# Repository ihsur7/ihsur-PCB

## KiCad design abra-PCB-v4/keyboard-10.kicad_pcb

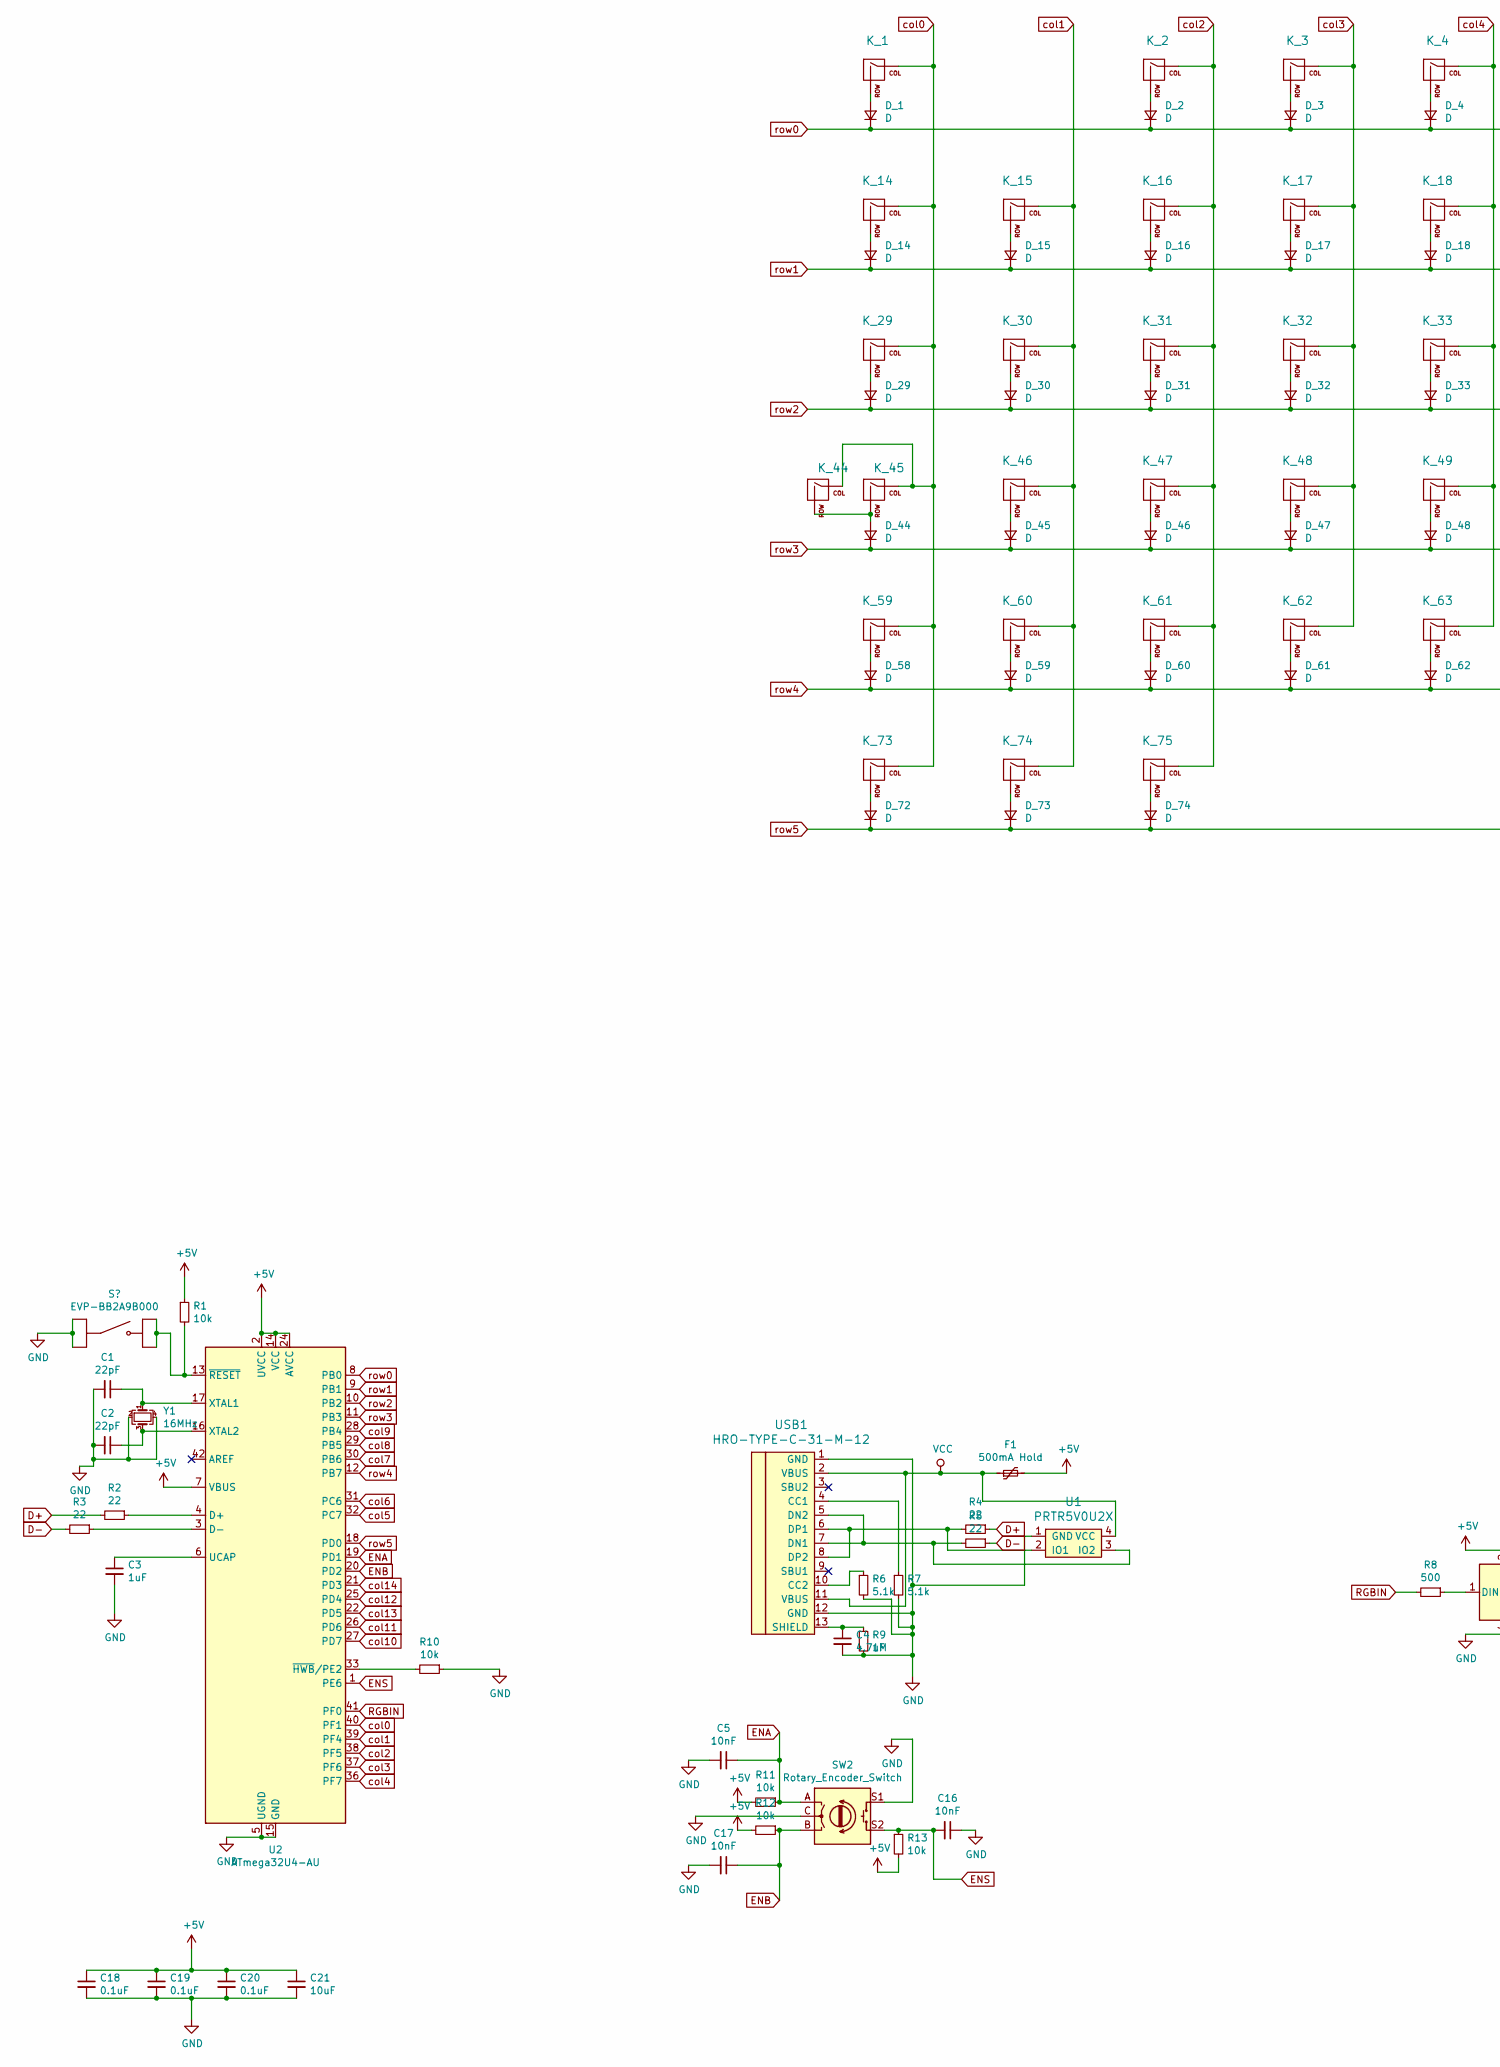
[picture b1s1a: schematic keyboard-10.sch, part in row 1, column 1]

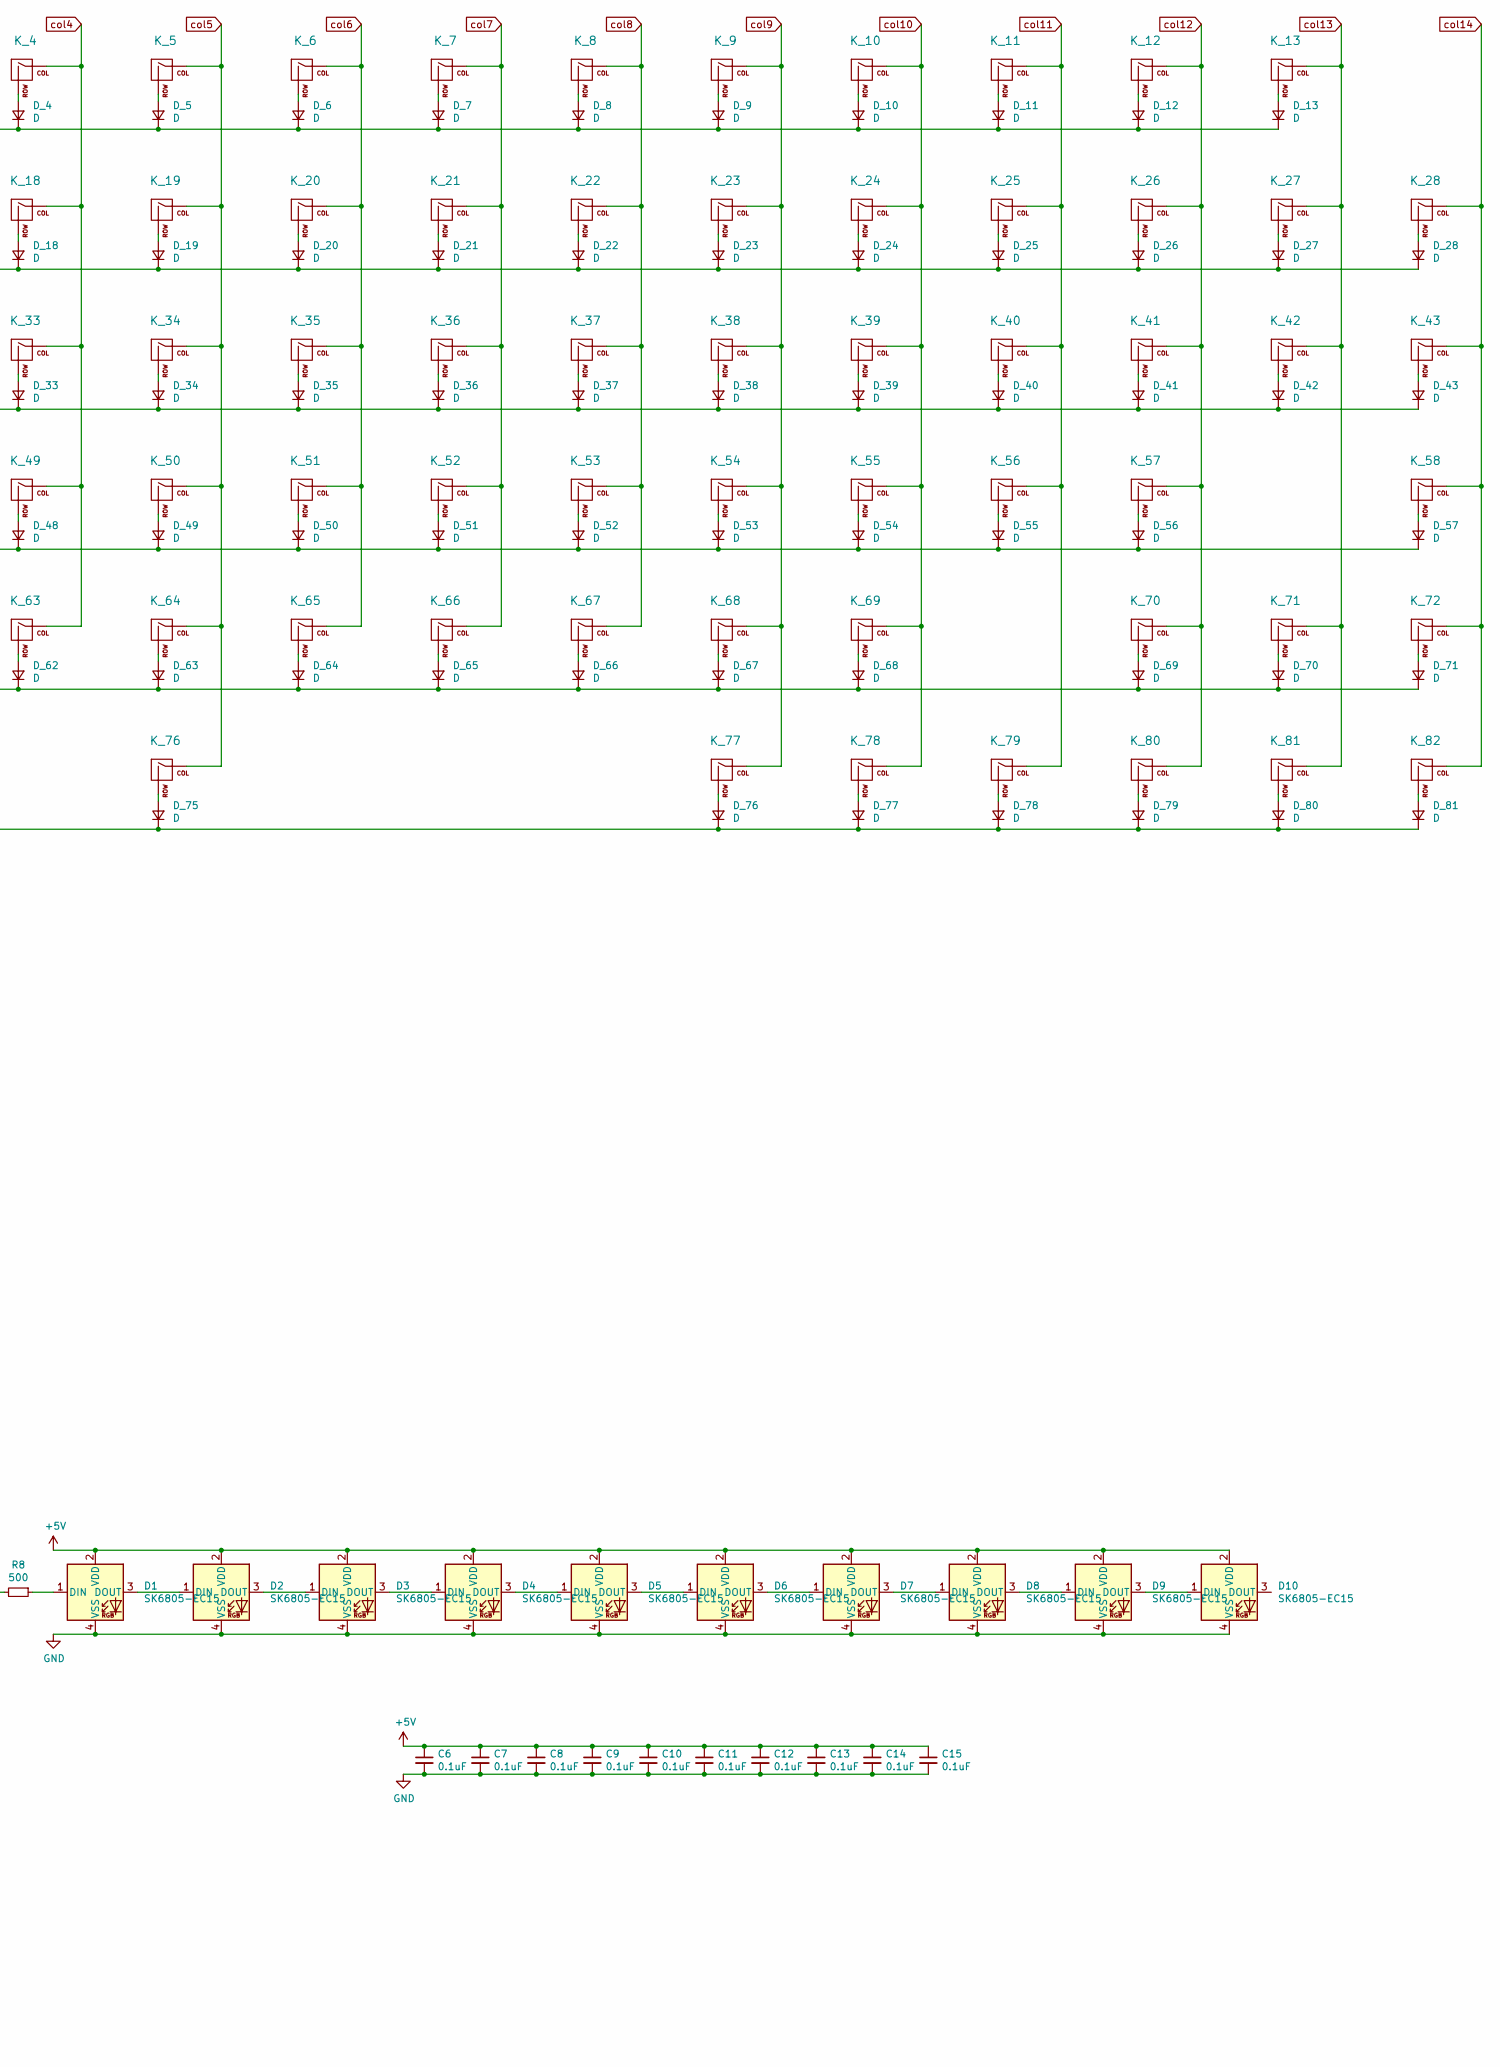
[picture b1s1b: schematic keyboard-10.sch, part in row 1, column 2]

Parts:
C1, C2: 22pF; C_0603
C3: 1uF; C_0603
C4: 4.7uF; C_0603
C5, C16, C17: 10nF; C_0603
C6, C7, C8, C9, C10, C11, C12, C13, C14, C15, C18, C19, C20: 0.1uF; C_0603
C21: 10uF; C_0603
D1, D2, D3, D4, D5, D6, D7, D8, D9, D10: SK6805-EC15; LED_SK6812_EC15_1.5x1.5mm
D_1, D_2, D_3, D_4, D_5, D_6, D_7, D_8, D_9, D_10, D_11, D_12, D_13, D_14, D_15, D_16, D_17, D_18, D_19, D_20, D_21, D_22, D_23, D_24, D_25, D_26, D_27, D_28, D_29, D_30, D_31, D_32, D_33, D_34, D_35, D_36, D_37, D_38, D_39, D_40, D_41, D_42, D_43, D_44, D_45, D_46, D_47, D_48, D_49, D_50, D_51, D_52, D_53, D_54, D_55, D_56, D_57, D_58, D_59, D_60, D_61, D_62, D_63, D_64, D_65, D_66, D_67, D_68, D_69, D_70, D_71, D_72, D_73, D_74, D_75, D_76, D_77, D_78, D_79, D_80, D_81: D; D_SOD-123
F1: 500mA Hold; Fuse_1812_4532
K_1, K_2, K_3, K_4, K_5, K_6, K_7, K_8, K_9, K_10, K_11, K_12, K_13, K_14, K_15, K_16, K_17, K_18, K_19, K_20, K_21, K_22, K_23, K_24, K_25, K_26, K_27, K_28, K_30, K_31, K_32, K_33, K_34, K_35, K_36, K_37, K_38, K_39, K_40, K_41, K_43, K_46, K_47, K_48, K_49, K_50, K_51, K_52, K_53, K_54, K_55, K_56, K_58, K_60, K_61, K_62, K_63, K_64, K_65, K_66, K_67, K_68, K_69, K_71, K_72, K_77, K_78, K_79, K_80, K_81, K_82: KEYSW; MXOnly-1U-NoLED
K_29, K_42: KEYSW; MXOnly-1.5U-NoLED
K_44, K_45, K_70: KEYSW; MXOnly-1.75U-NoLED
K_57, K_59: KEYSW; MXOnly-2.25U-NoLED
K_73, K_74, K_75: KEYSW; MXOnly-1.25U-NoLED
K_76: KEYSW; MXOnly-6.25U-NoLED
R1, R10, R11, R12, R13: 10k; R_0805
R2, R3, R4, R5: 22; R_0805
R6, R7: 5.1k; R_0805
R8: 500; R_0805
R9: 1M; R_0805
SW2: Rotary_Encoder_Switch; RotaryEncoder_Alps_EC11E-Switch_Vertical_H20mm
U1: PRTR5V0U2X; SOT143B
U2: ATmega32U4-AU; TQFP-44_10x10mm_P0.8mm
USB1: HRO-TYPE-C-31-M-12; HRO-TYPE-C-31-M-12-HandSoldering
Y1: 16MHz; Crystal_SMD_3225-4pin_3.2x2.5mm

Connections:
+5V: C6.1, C7.1, C8.1, C9.1, C10.1, C11.1, C12.1, C13.1, C14.1, C15.1, C18.1, C19.1, C20.1, C21.1, D1.2 (VDD), D2.2 (VDD), D3.2 (VDD), D4.2 (VDD), D5.2 (VDD), D6.2 (VDD), D7.2 (VDD), D8.2 (VDD), D9.2 (VDD), D10.2 (VDD), F1.2, R1.1, R11.2, R12.2, R13.2, U2.2 (UVCC), U2.7 (VBUS), U2.14 (VCC), U2.24 (AVCC), U2.34 (VCC), U2.44 (AVCC)
D+: R2.2, R4.1
D-: R3.2, R5.1
ENA: C5.1, R11.1, SW2.A, U2.19 (PD1)
ENB: C17.1, R12.1, SW2.B, U2.20 (PD2)
ENS: C16.2, R13.1, SW2.S2, U2.1 (PE6)
GND: C1.2, C2.2, C3.2, C4.2, C5.2, C6.2, C7.2, C8.2, C9.2, C10.2, C11.2, C12.2, C13.2, C14.2, C15.2, C16.1, C17.2, C18.2, C19.2, C20.2, C21.2, D1.4 (VSS), D2.4 (VSS), D3.4 (VSS), D4.4 (VSS), D5.4 (VSS), D6.4 (VSS), D7.4 (VSS), D8.4 (VSS), D9.4 (VSS), D10.4 (VSS), R6.2, R7.2, R9.2, R10.1, SW2.C, SW2.S1, U1.1 (GND), U2.5 (UGND), U2.15 (GND), U2.23 (GND), U2.35 (GND), U2.43 (GND), USB1.1 (GND), USB1.12 (GND), Y1.2, Y1.4; also elsewhere on the board
unnamed: C1.1, U2.17 (XTAL1), Y1.1
unnamed: C2.1, U2.16 (XTAL2), Y1.3
unnamed: C3.1, U2.6 (UCAP)
unnamed: C4.1, R9.1, USB1.13 (SHIELD)
unnamed: D1.1 (DIN), R8.1
unnamed: D1.3 (DOUT), D2.1 (DIN)
unnamed: D2.3 (DOUT), D3.1 (DIN)
unnamed: D3.3 (DOUT), D4.1 (DIN)
unnamed: D4.3 (DOUT), D5.1 (DIN)
unnamed: D5.3 (DOUT), D6.1 (DIN)
unnamed: D6.3 (DOUT), D7.1 (DIN)
unnamed: D7.3 (DOUT), D8.1 (DIN)
unnamed: D8.3 (DOUT), D9.1 (DIN)
unnamed: D9.3 (DOUT), D10.1 (DIN)
unnamed: D_1.2 (A), K_1.2 (ROW)
unnamed: D_2.2 (A), K_2.2 (ROW)
unnamed: D_3.2 (A), K_3.2 (ROW)
unnamed: D_4.2 (A), K_4.2 (ROW)
unnamed: D_5.2 (A), K_5.2 (ROW)
unnamed: D_6.2 (A), K_6.2 (ROW)
unnamed: D_7.2 (A), K_7.2 (ROW)
unnamed: D_8.2 (A), K_8.2 (ROW)
unnamed: D_9.2 (A), K_9.2 (ROW)
unnamed: D_10.2 (A), K_10.2 (ROW)
unnamed: D_11.2 (A), K_11.2 (ROW)
unnamed: D_12.2 (A), K_12.2 (ROW)
unnamed: D_13.2 (A), K_13.2 (ROW)
unnamed: D_14.2 (A), K_14.2 (ROW)
unnamed: D_15.2 (A), K_15.2 (ROW)
unnamed: D_16.2 (A), K_16.2 (ROW)
unnamed: D_17.2 (A), K_17.2 (ROW)
unnamed: D_18.2 (A), K_18.2 (ROW)
unnamed: D_19.2 (A), K_19.2 (ROW)
unnamed: D_20.2 (A), K_20.2 (ROW)
unnamed: D_21.2 (A), K_21.2 (ROW)
unnamed: D_22.2 (A), K_22.2 (ROW)
unnamed: D_23.2 (A), K_23.2 (ROW)
unnamed: D_24.2 (A), K_24.2 (ROW)
unnamed: D_25.2 (A), K_25.2 (ROW)
unnamed: D_26.2 (A), K_26.2 (ROW)
unnamed: D_27.2 (A), K_27.2 (ROW)
unnamed: D_28.2 (A), K_28.2 (ROW)
unnamed: D_29.2 (A), K_29.2 (ROW)
unnamed: D_30.2 (A), K_30.2 (ROW)
unnamed: D_31.2 (A), K_31.2 (ROW)
unnamed: D_32.2 (A), K_32.2 (ROW)
unnamed: D_33.2 (A), K_33.2 (ROW)
unnamed: D_34.2 (A), K_34.2 (ROW)
unnamed: D_35.2 (A), K_35.2 (ROW)
unnamed: D_36.2 (A), K_36.2 (ROW)
unnamed: D_37.2 (A), K_37.2 (ROW)
unnamed: D_38.2 (A), K_38.2 (ROW)
unnamed: D_39.2 (A), K_39.2 (ROW)
unnamed: D_40.2 (A), K_40.2 (ROW)
unnamed: D_41.2 (A), K_41.2 (ROW)
unnamed: D_42.2 (A), K_42.2 (ROW)
unnamed: D_43.2 (A), K_43.2 (ROW)
unnamed: D_44.2 (A), K_44.2 (ROW), K_45.2 (ROW)
unnamed: D_45.2 (A), K_46.2 (ROW)
unnamed: D_46.2 (A), K_47.2 (ROW)
unnamed: D_47.2 (A), K_48.2 (ROW)
unnamed: D_48.2 (A), K_49.2 (ROW)
unnamed: D_49.2 (A), K_50.2 (ROW)
unnamed: D_50.2 (A), K_51.2 (ROW)
unnamed: D_51.2 (A), K_52.2 (ROW)
unnamed: D_52.2 (A), K_53.2 (ROW)
unnamed: D_53.2 (A), K_54.2 (ROW)
unnamed: D_54.2 (A), K_55.2 (ROW)
unnamed: D_55.2 (A), K_56.2 (ROW)
unnamed: D_56.2 (A), K_57.2 (ROW)
unnamed: D_57.2 (A), K_58.2 (ROW)
unnamed: D_58.2 (A), K_59.2 (ROW)
unnamed: D_59.2 (A), K_60.2 (ROW)
unnamed: D_60.2 (A), K_61.2 (ROW)
unnamed: D_61.2 (A), K_62.2 (ROW)
unnamed: D_62.2 (A), K_63.2 (ROW)
unnamed: D_63.2 (A), K_64.2 (ROW)
unnamed: D_64.2 (A), K_65.2 (ROW)
unnamed: D_65.2 (A), K_66.2 (ROW)
unnamed: D_66.2 (A), K_67.2 (ROW)
unnamed: D_67.2 (A), K_68.2 (ROW)
unnamed: D_68.2 (A), K_69.2 (ROW)
unnamed: D_69.2 (A), K_70.2 (ROW)
unnamed: D_70.2 (A), K_71.2 (ROW)
unnamed: D_71.2 (A), K_72.2 (ROW)
unnamed: D_72.2 (A), K_73.2 (ROW)
unnamed: D_73.2 (A), K_74.2 (ROW)
unnamed: D_74.2 (A), K_75.2 (ROW)
unnamed: D_75.2 (A), K_76.2 (ROW)
unnamed: D_76.2 (A), K_77.2 (ROW)
unnamed: D_77.2 (A), K_78.2 (ROW)
unnamed: D_78.2 (A), K_79.2 (ROW)
unnamed: D_79.2 (A), K_80.2 (ROW)
unnamed: D_80.2 (A), K_81.2 (ROW)
unnamed: D_81.2 (A), K_82.2 (ROW)
unnamed 102: R1.2, U2.13 (~RESET); also elsewhere on the board
unnamed: R2.1, U2.4 (D+)
unnamed: R3.1, U2.3 (D-)
unnamed: R4.2, U1.2 (IO1), USB1.6 (DP1), USB1.8 (DP2)
unnamed: R5.2, U1.3 (IO2), USB1.5 (DN2), USB1.7 (DN1)
unnamed: R6.1, USB1.10 (CC2)
unnamed: R7.1, USB1.4 (CC1)
unnamed: R10.2, U2.33 (~HWB~/PE2)
RGBIN: R8.2, U2.41 (PF0)
VCC: F1.1, U1.4 (VCC), USB1.2 (VBUS), USB1.11 (VBUS)
col0: K_1.1 (COL), K_14.1 (COL), K_29.1 (COL), K_44.1 (COL), K_45.1 (COL), K_59.1 (COL), K_73.1 (COL), U2.40 (PF1)
col1: K_15.1 (COL), K_30.1 (COL), K_46.1 (COL), K_60.1 (COL), K_74.1 (COL), U2.39 (PF4)
col2: K_2.1 (COL), K_16.1 (COL), K_31.1 (COL), K_47.1 (COL), K_61.1 (COL), K_75.1 (COL), U2.38 (PF5)
col3: K_3.1 (COL), K_17.1 (COL), K_32.1 (COL), K_48.1 (COL), K_62.1 (COL), U2.37 (PF6)
col4: K_4.1 (COL), K_18.1 (COL), K_33.1 (COL), K_49.1 (COL), K_63.1 (COL), U2.36 (PF7)
col5: K_5.1 (COL), K_19.1 (COL), K_34.1 (COL), K_50.1 (COL), K_64.1 (COL), K_76.1 (COL), U2.32 (PC7)
col6: K_6.1 (COL), K_20.1 (COL), K_35.1 (COL), K_51.1 (COL), K_65.1 (COL), U2.31 (PC6)
col7: K_7.1 (COL), K_21.1 (COL), K_36.1 (COL), K_52.1 (COL), K_66.1 (COL), U2.30 (PB6)
col8: K_8.1 (COL), K_22.1 (COL), K_37.1 (COL), K_53.1 (COL), K_67.1 (COL), U2.29 (PB5)
col9: K_9.1 (COL), K_23.1 (COL), K_38.1 (COL), K_54.1 (COL), K_68.1 (COL), K_77.1 (COL), U2.28 (PB4)
col10: K_10.1 (COL), K_24.1 (COL), K_39.1 (COL), K_55.1 (COL), K_69.1 (COL), K_78.1 (COL), U2.27 (PD7)
col11: K_11.1 (COL), K_25.1 (COL), K_40.1 (COL), K_56.1 (COL), K_79.1 (COL), U2.26 (PD6)
col12: K_12.1 (COL), K_26.1 (COL), K_41.1 (COL), K_57.1 (COL), K_70.1 (COL), K_80.1 (COL), U2.25 (PD4)
col13: K_13.1 (COL), K_27.1 (COL), K_42.1 (COL), K_71.1 (COL), K_81.1 (COL), U2.22 (PD5)
col14: K_28.1 (COL), K_43.1 (COL), K_58.1 (COL), K_72.1 (COL), K_82.1 (COL), U2.21 (PD3)
row0: D_1.1 (K), D_2.1 (K), D_3.1 (K), D_4.1 (K), D_5.1 (K), D_6.1 (K), D_7.1 (K), D_8.1 (K), D_9.1 (K), D_10.1 (K), D_11.1 (K), D_12.1 (K), D_13.1 (K), U2.8 (PB0)
row1: D_14.1 (K), D_15.1 (K), D_16.1 (K), D_17.1 (K), D_18.1 (K), D_19.1 (K), D_20.1 (K), D_21.1 (K), D_22.1 (K), D_23.1 (K), D_24.1 (K), D_25.1 (K), D_26.1 (K), D_27.1 (K), D_28.1 (K), U2.9 (PB1)
row2: D_29.1 (K), D_30.1 (K), D_31.1 (K), D_32.1 (K), D_33.1 (K), D_34.1 (K), D_35.1 (K), D_36.1 (K), D_37.1 (K), D_38.1 (K), D_39.1 (K), D_40.1 (K), D_41.1 (K), D_42.1 (K), D_43.1 (K), U2.10 (PB2)
row3: D_44.1 (K), D_45.1 (K), D_46.1 (K), D_47.1 (K), D_48.1 (K), D_49.1 (K), D_50.1 (K), D_51.1 (K), D_52.1 (K), D_53.1 (K), D_54.1 (K), D_55.1 (K), D_56.1 (K), D_57.1 (K), U2.11 (PB3)
row4: D_58.1 (K), D_59.1 (K), D_60.1 (K), D_61.1 (K), D_62.1 (K), D_63.1 (K), D_64.1 (K), D_65.1 (K), D_66.1 (K), D_67.1 (K), D_68.1 (K), D_69.1 (K), D_70.1 (K), D_71.1 (K), U2.12 (PB7)
row5: D_72.1 (K), D_73.1 (K), D_74.1 (K), D_75.1 (K), D_76.1 (K), D_77.1 (K), D_78.1 (K), D_79.1 (K), D_80.1 (K), D_81.1 (K), U2.18 (PD0)

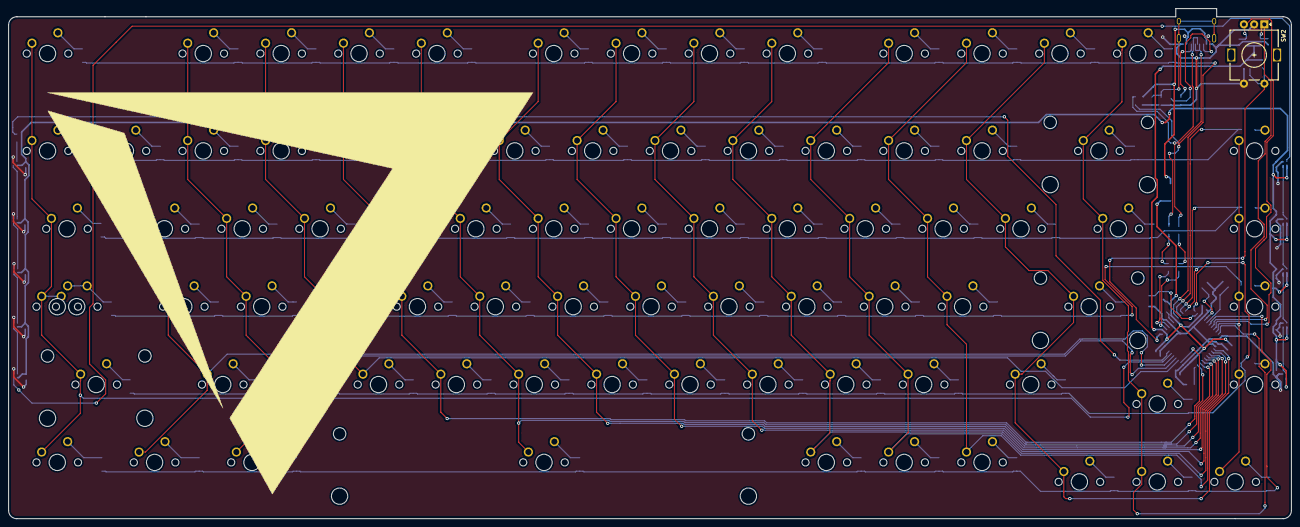
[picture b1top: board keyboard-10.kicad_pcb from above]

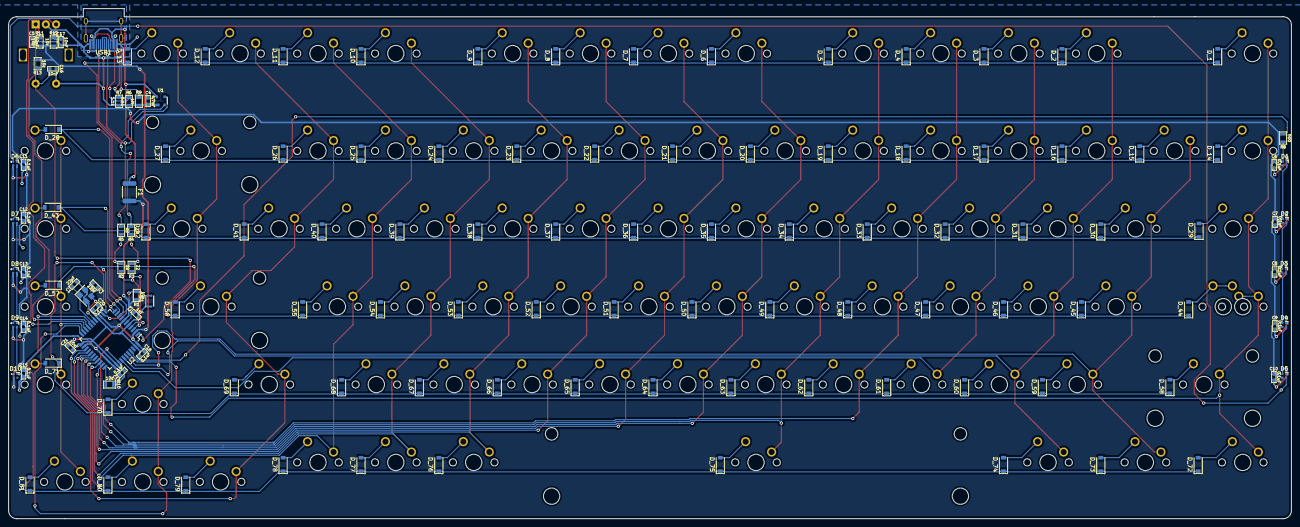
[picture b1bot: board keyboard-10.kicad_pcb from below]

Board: 2 copper layers, 313.8 x 124.8 mm, 214 parts (131 on the bottom side), 133 nets.

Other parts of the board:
S1: EVP-BB2A9B000; SW_EVP-BB2A9B000

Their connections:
GND: S1.A1, S1.A2; also elsewhere on the board
unnamed 102: S1.B1, S1.B2; also elsewhere on the board
